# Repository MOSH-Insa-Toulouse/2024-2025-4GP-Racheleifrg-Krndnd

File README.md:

# 2024-2025-4GP-Racheleifrg-Krndnd

# Graphite-based sensor project

**Students**: Rachele Iffrig, Karine Dandy

Département Génie Physique

INSA Toulouse

## Project Description

The aim of this project is to determine the main characteristics of a low-tech strain sensor, as introduced in the paper “Pencil Drawn Strain Gauges and Chemiresistors on Paper”  by Cheng-Wei Lin, Zhibo Zhao, Jaemyung Kim & Jiaxing Huang, published on Nature in 2014, and to compare them with those of an industrial flex sensor. To do so, both sensors are managed by an Arduino Uno board. On this board we also have an OLED screen in order to display the data, and we navigate through the menus using a rotary encoder. The data are sent to an Android application via a Bluetooth® module.<br> <br>
You can recreate this project from scratch, as we have provided everything — from the PCB design using KiCad, the Arduino code, and the Android app, to the test bench setup used to compare both sensors and create the graphite sensor’s datasheet. 

## Content

In this GitHub repository you will find independent folders for each part of our project.

1) **KiCad**: The KiCad folder contains our project (KiCad-Shield-Uno-FlexSensor) and all the libraries we created and used. It is ready to use, you will only need to download KiCad on your laptop. 
   
2) **Arduino code**: The Arduino folder contains 2 different codes: 
     *code_Flex_OR_graphite_datas_sent_via_bluetooth.ino* and *code_Flex_AND_graphite_datas_sent_via_bluetooth*. Both codes calculate the resistance of the industrial strain gauge sensor as well as the graphite-based one, and are using the rotary encoder to navigate through the different menus displayed on the OLED screen. The difference between the two codes comes with what data we are sending via Bluetooth®. In the first code, at the beginning, the user chooses which sensor’s information they want to plot in the app. The second code sends data from both sensors simultaneously: both resistances are plotted, but with less precision. 
   
3) **Android App**: The Android App folder contains all the information concerning the two apps, made with MIT App Inventor, that are receiving all the data sent via Bluetooth®. With these apps, compatible with Android, you can either plot the resistances of both the flex and graphite sensors simultaneously, or choose to plot only one of them, depending on the code you chose.      

4) **Bench test**: The Bench test folder contains pictures of our graphite-based sensor, and the bench test used.

5) **Results graphite based sensor flex_sensor**: All the results obtained and presented in the sensor's datasheet can be found on the Excel file "Results_graphite-based_sensor_and_flex_sensor". All the calculations made to obtain the relative resistance variation and the deformations are also included in this Excel file. 
   
6) **Sensor project presentation**: The Sensor project presentation folder contains a PowerPoint in which we explain the different steps of our project, the difficulties we faced and the results we obtained.

7) **Datasheet**: The datasheet folder contains the datasheet of our graphite-based sensor. This document describes the main features of the graphite-based sensor, its working principle, its working conditions, and presents the results of the comparison between the flex sensor and graphite-based one. This graphite-based sensor can measure deformations up to 0.006, at room temperature. Higher deformations can break the graphite sensor. 

We found that the hardest pencil (H) was the most sensitive. The same conclusion was also reached by Wei et al. Measurement errors may
have influenced our results, or we may have omitted other unknown factors. Nevertheless, a potential
application for this technology can be observed when using hard pencils. With further material and
experimental modifications, our handmade graphite sensor could be optimized.
 
## Physic behind the low tech strain gauges

This graphite-based sensor works similarly to a strain gauge and can detect mechanical deformations under tension or compression. 
It can measure resistances of the order of the giga-ohm. The working principle relies on the relationship between the average nanoparticle distance and the resistance. 
Due to the granular property of the graphite, under tension, the layer stretches, increasing the distance between the nanoparticles (Figure 1). 
According to percolation theory, the material’s conductivity decreases, while its resistance increases. 
In compression, the distance between the nanoparticles is reduced, and the resistance decreases as more electrical paths are present.

Figure 1 – Working principle of the graphite-based sensor in compression and tension. Extracted from
“Pencil Drawn Strain Gauges and Chemiresistors on Paper”, by Cheng-Wei et al.

## Necessary components to carry out this project

* 1 graphite-based paper sensor
* 1 flex sensor
* 1 LTC1050 operational amplifier
* 1 MCP41050 digital potentiometer
* 1 KY-040 rotary encoder
* 1 Arduino UNO
* 1 OLED screen
* 1 HC-05 Bluetooth® module
* Resistances: 1kΩ, 10kΩ, 100kΩ, 100kΩ
* Capacitors: 100nF, 100nF, 1µF
* For the test bench: 1 round glass, 1 glue stick, 1 tape, 1 toothpaste cap, 1 liquid correction fluid (Tipp-Ex)

<figure>
  
  <figcaption>Figure 2 - Image of the complete project.</figcaption>
</figure>

## How to use

The first step is to create the electrical amplifier circuit and the footprint of the PCB on KiCad. Our complete KiCad project and all the libraries used can be found in the KiCad folder.  

The second step is to order or fabricate the PCB and mount it on an Arduino UNO board. 

By using similar features as our graphite-based sensor (Figure 3), and our Arduino code (available in the Arduino code folder), it is possible to measure a resistance for a given deformation. 

Figure 3 – Representation of our graphite-based sensor. The units are in mm. Extracted from the work
of Paul Besnard and Niels Brun, available on GitHub.

This graphite-based sensor can measure deformations up to 0.006, at room temperature. This sensor can
be made with other paper and graphite pencils to improve sensitivity. We highly recommend
the use of thin papers and harder graphite pencils. 

### Project Assembly

1) Create the PCB using the file *KiCad-Shield-Uno-FlexSensor.kicad_pro* (KiCad/KiCad-Shield-Uno-FlexSensor.kicad_pro) found in the **KiCad** folder. NB: you can also use a breadboard and follow the schematic from the following file: *KiCad-Shield-Uno-FlexSensor.kicad_sch* (KiCad/KiCad-Shield-Uno-FlexSensor.kicad_sch)
2) Solder the components following the PCB and schematic that can be found in the same **KiCad** folder.
3) Connect the PCB to the Arduino, and then connect the Arduino to a PC via USB.
4) Choose one of the two codes from the **Arduino** folder based on your needs.      
5) Once the program is open in the Arduino IDE, select **Arduino Uno** as the board.
6) Run the code.
7) If you chose: *code_Felex_OR_graphite_datas_sent_via_bluetooth.ino* select the data you want to plot on the app, following the instructions that appear on the Serial.

### OLED's Menus
When you upload the code to the Arduino, the OLED screen lights up. On the OLED display, you can access **three different menus**:

1. **Potentiometer Selection Menu**  
   Allows you to choose between **four different potentiometer values**.

2. **Flex Sensor Data Menu**  
   Displays real-time data from the **flex sensor**.

3. **Graphite Sensor Data Menu**  
   Displays real-time data from the **graphite sensor**.<br> <br>
To switch between menus, press the rotary encoder. Inside each menu, rotate the encoder to scroll through the available options. To select an option (if applicable), press the rotary encoder's switch.

### Android App
1. **Pair your smartphone with the HC-05 Bluetooth module.** If a code is requested, enter **0000** or **1234**.

2. **Download the `.exe` file to your smartphone** by scanning the **QR code** in the folder of the Android App.

3. **Open the application**
4. **Grant the necessary permissions** to the application so it can detect Bluetooth® devices connected to your Android.This can be done via your phone’s **Bluetooth® or app settings**.

5.  **Click on the Bluetooth® button**.

6. **Select the HC-05 module** from the list of available devices.

7. **Select the potentiometer value** that you previously chose using the **OLED menu** on the Arduino.

8. **If you are using the Flex or Graph app**,select the resistance value you chose at the beginning of the program from the **drop-down menu**.

9. **Start data acquisition** by pressing the **Start** button.

10. **Stop data acquisition** by pressing the **Stop** button.

<figure>
  
  <figcaption>Figure 4 - Image of the screen when we open the app</figcaption>
</figure>

### Test Bench

To test and compare our graphite-based sensor to a commercial sensor (the flex sensor), we used five objects with different diameters. We then fabricated and tested our graphite-based sensor using three different types of pencils: 2B, H, and HB.   

Figure 5 – Photograph of the objects used with the corresponding diameters during the bench test.

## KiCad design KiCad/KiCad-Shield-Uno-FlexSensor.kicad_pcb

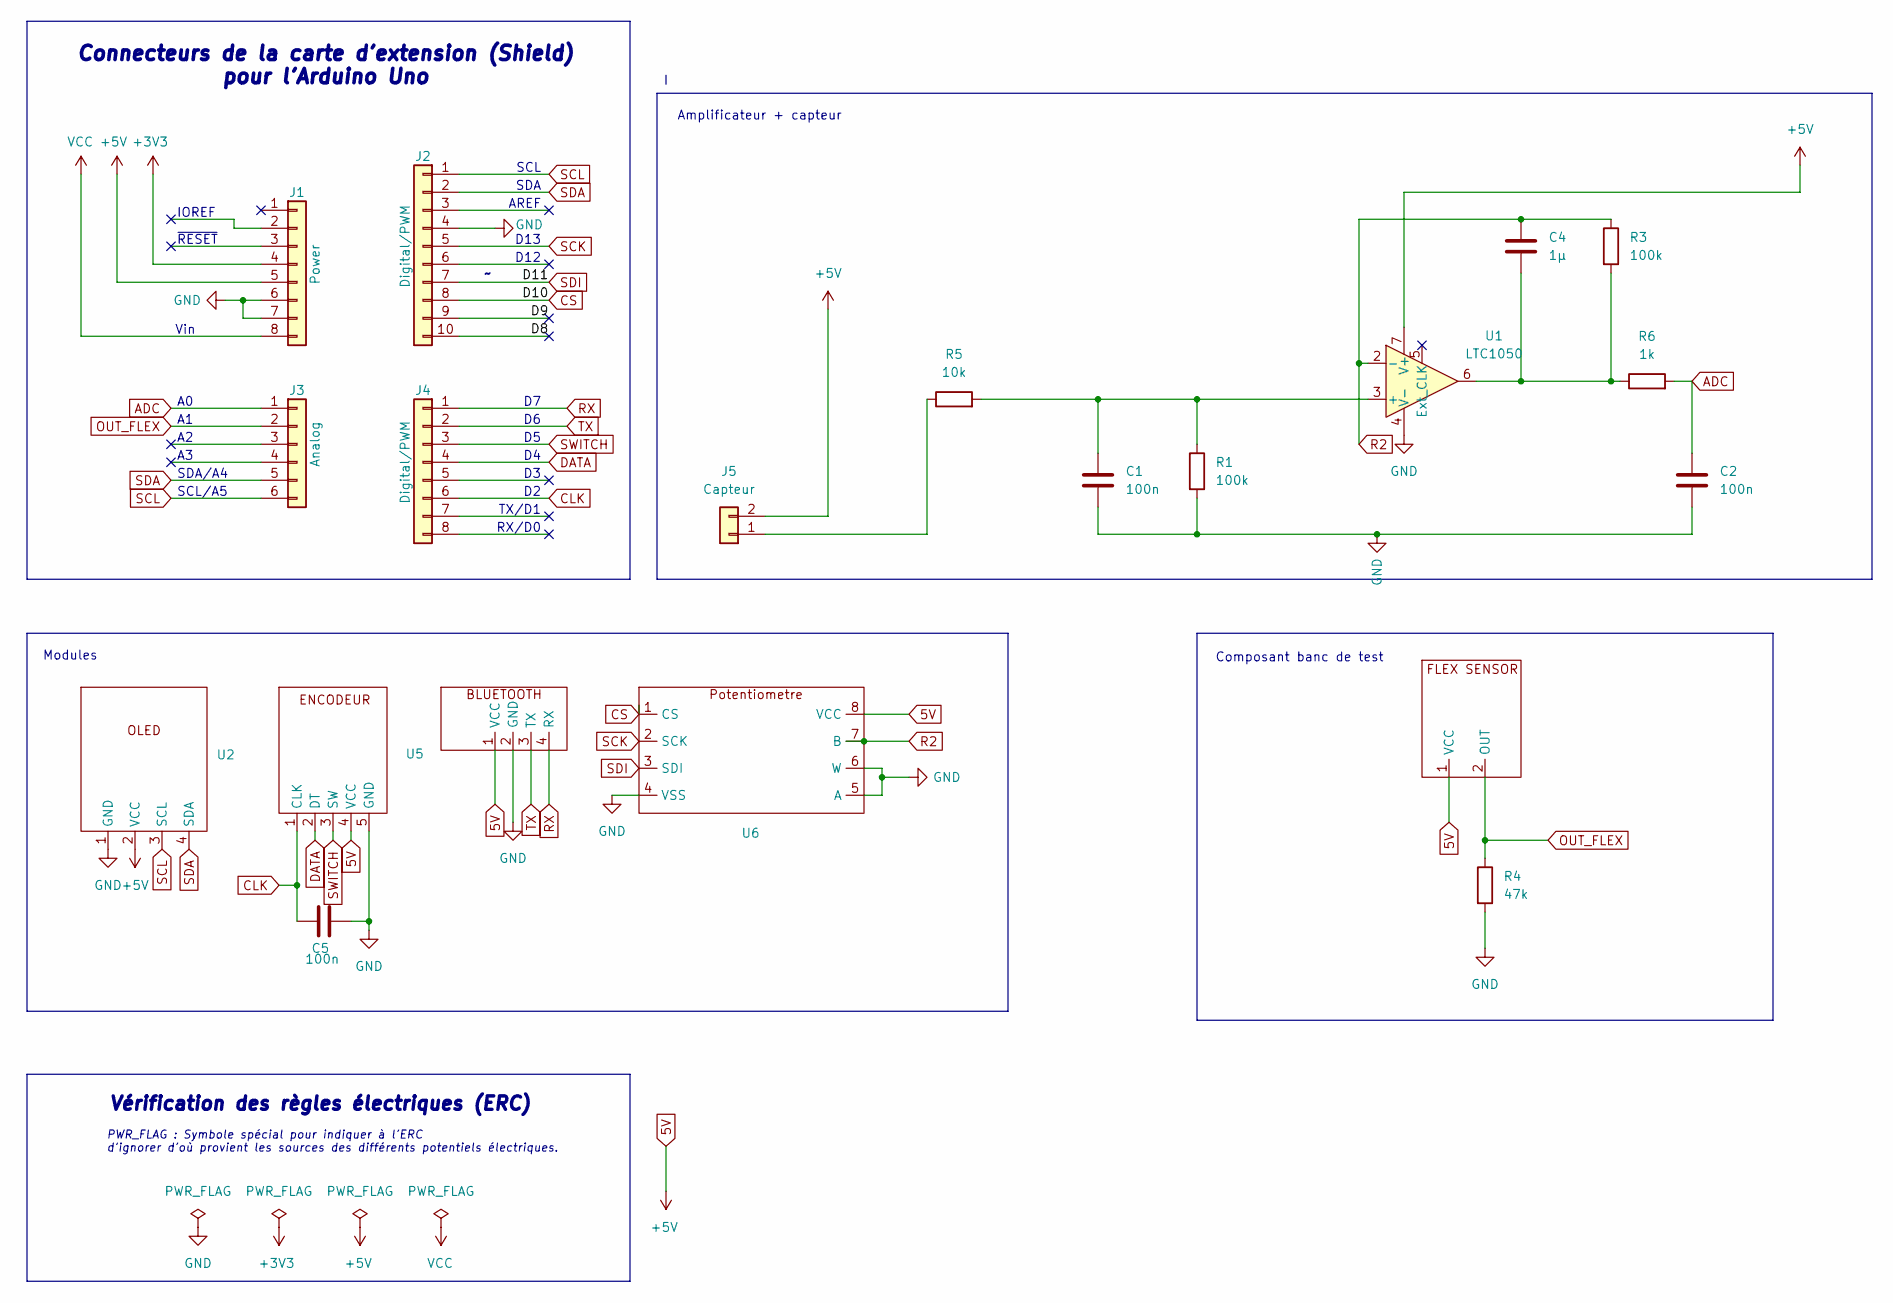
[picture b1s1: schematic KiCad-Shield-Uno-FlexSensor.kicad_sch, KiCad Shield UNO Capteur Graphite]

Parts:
C1: 100n; C_Disc_D5.0mm_W2.5mm_P5.00mm
C2: 100n; C_Disc_D4.7mm_W2.5mm_P5.00mm
C4: 1µ; C_Rect_L7.0mm_W4.5mm_P5.00mm
C5: 100n; C_Disc_D6.0mm_W2.5mm_P5.00mm
J1: Power; PinSocket_1x08_P2.54mm_Vertical
J2: Digital/PWM; PinSocket_1x10_P2.54mm_Vertical
J3: Analog; PinSocket_1x06_P2.54mm_Vertical
J4: Digital/PWM; PinSocket_1x08_P2.54mm_Vertical
J5: Capteur; PinSocket_1x02_P2.54mm_Vertical
R1, R3: 100k; R_Axial_DIN0207_L6.3mm_D2.5mm_P10.16mm_Horizontal
R4: 47k; R_Axial_DIN0207_L6.3mm_D2.5mm_P5.08mm_Vertical
R5: 10k; R_Axial_DIN0207_L6.3mm_D2.5mm_P10.16mm_Horizontal
R6: 1k; R_Axial_DIN0207_L6.3mm_D2.5mm_P10.16mm_Horizontal
U1: LTC1050
U2: OLED
U3: Flex sensor
U4: bluetooth
U5: ENCODEUR
U6: Potentiometre

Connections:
5V: J1.5, J5.2, U1.7 (V+), U2.2 (VCC), U3.1 (VCC), U4.1 (VCC), U5.4 (VCC), U6.8 (VCC)
+3V3: J1.4
/D8: J2.10
/D9: J2.9
ADC: C2.1, J3.1, R6.2
CLK: C5.1, J4.6, U5.1 (CLK)
CS: J2.8, U6.1 (CS)
DATA: J4.4, U5.2 (DT)
GND: C1.2, C2.2, C5.2, J1.6, J1.7, J2.4, R1.2, R4.2, U1.4 (V-), U2.1 (GND), U4.2 (GND), U5.5 (GND), U6.4 (VSS), U6.5 (A), U6.6 (W)
unnamed: C4.2, R3.2, R6.1, U1.6
unnamed: J5.1, R5.1
unnamed: C1.1, R1.1, R5.2, U1.3 (+)
OUT_FLEX: J3.2, R4.1, U3.2 (OUT)
R2: C4.1, R3.1, U1.2 (-), U6.7 (B)
RX: J4.1, U4.4 (RX)
SCK: J2.5, U6.2 (SCK)
SCL: J2.1, J3.6, U2.3 (SCL)
SDA: J2.2, J3.5, U2.4 (SDA)
SDI: J2.7, U6.3 (SDI)
SWITCH: J4.3, U5.3 (SW)
TX: J4.2, U4.3 (TX)
VCC: J1.8

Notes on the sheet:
Composant banc de test
AREF
SDA/A4
D12
Amplificateur + capteur
~{RESET}
RX/D0
TX/D1
D13
Vin
SDA
Vérification des règles électriques (ERC)
Connecteurs de la carte d'extension (Shield) pour l'Arduino Uno
Modules
SCL/A5
SCL
IOREF
PWR_FLAG : Symbole spécial pour indiquer à l'ERC d'ignorer d'où provient les sources des différents potentiels électriques.

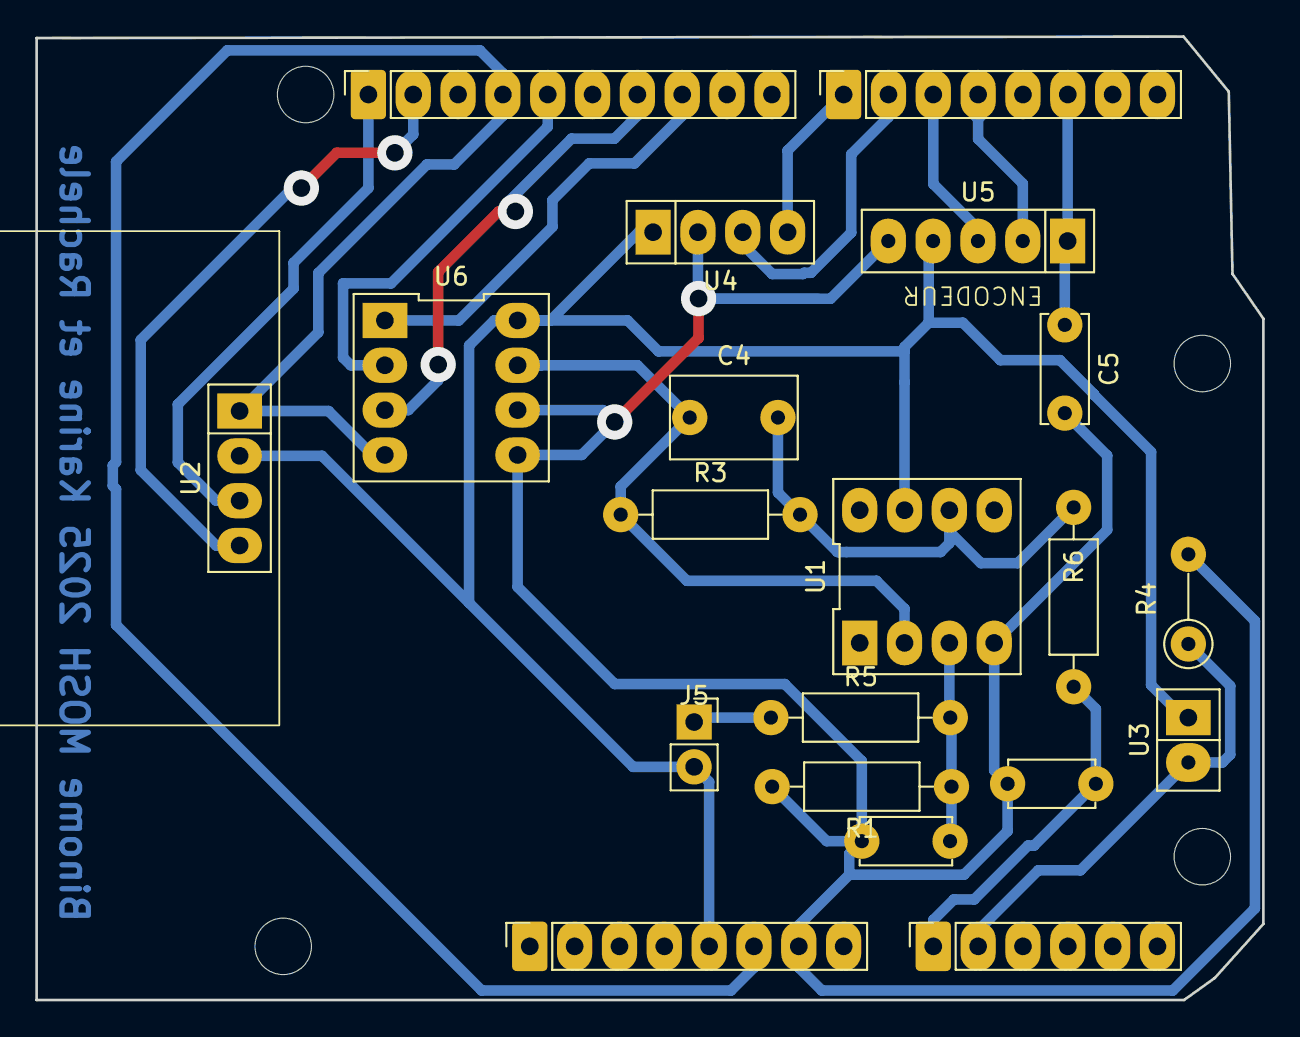
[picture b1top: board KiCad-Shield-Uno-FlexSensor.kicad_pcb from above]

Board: 2 copper layers, 69.5 x 54.6 mm, 24 parts (0 on the bottom side), 18 nets.

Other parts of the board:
MH1, MH2, MH3, MH4: MountingHole_3.2mm

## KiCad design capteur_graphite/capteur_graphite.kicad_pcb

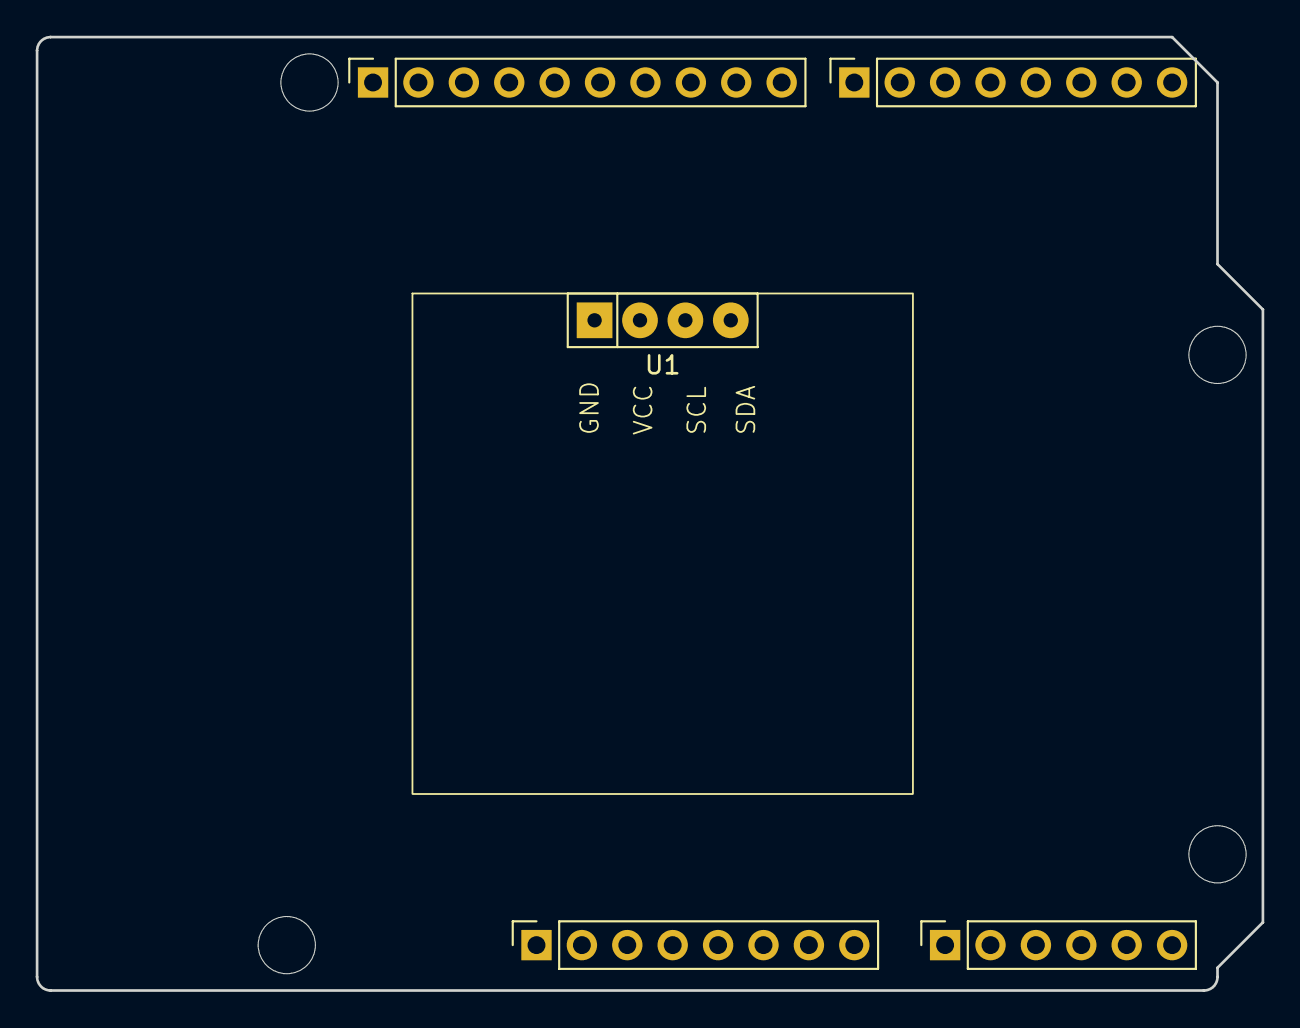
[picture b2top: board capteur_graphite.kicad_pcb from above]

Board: 2 copper layers, 68.6 x 53.3 mm, 9 parts (0 on the bottom side), 3 nets, no tracks yet.

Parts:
J1: Power; PinSocket_1x08_P2.54mm_Vertical
J2: Digital/PWM; PinSocket_1x10_P2.54mm_Vertical
J3: Analog; PinSocket_1x06_P2.54mm_Vertical
J4: Digital/PWM; PinSocket_1x08_P2.54mm_Vertical
MH1, MH2, MH3, MH4: MountingHole_3.2mm
U1: OLED1306

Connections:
/SCL/A5: J2.1, J3.6
/SDA/A4: J2.2, J3.5
GND: J1.6, J1.7, J2.4

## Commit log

2025-02-21 modified: README.md
2025-02-21 Update README.md
    hey
2025-02-21 New commit
2025-02-21 actualisation
2025-02-21 Modif
2025-02-21 Liberté
2025-05-28 Update README.md Rachele
2025-05-28 Update README.md corrections
2025-05-29 Added last folders
    Added the bench test, KiCAD, the results, datasheet, and the Power Point presentation
2025-05-30 Rename code_Felex_OR_graphite_datas_sent_via_bluetooth.ino to code_Flex_OR_graphite_datas_sent_via_bluetooth.ino
2025-05-30 Update README.md
    Minor changes
2025-05-30 Update README.md
    Minor corrections
